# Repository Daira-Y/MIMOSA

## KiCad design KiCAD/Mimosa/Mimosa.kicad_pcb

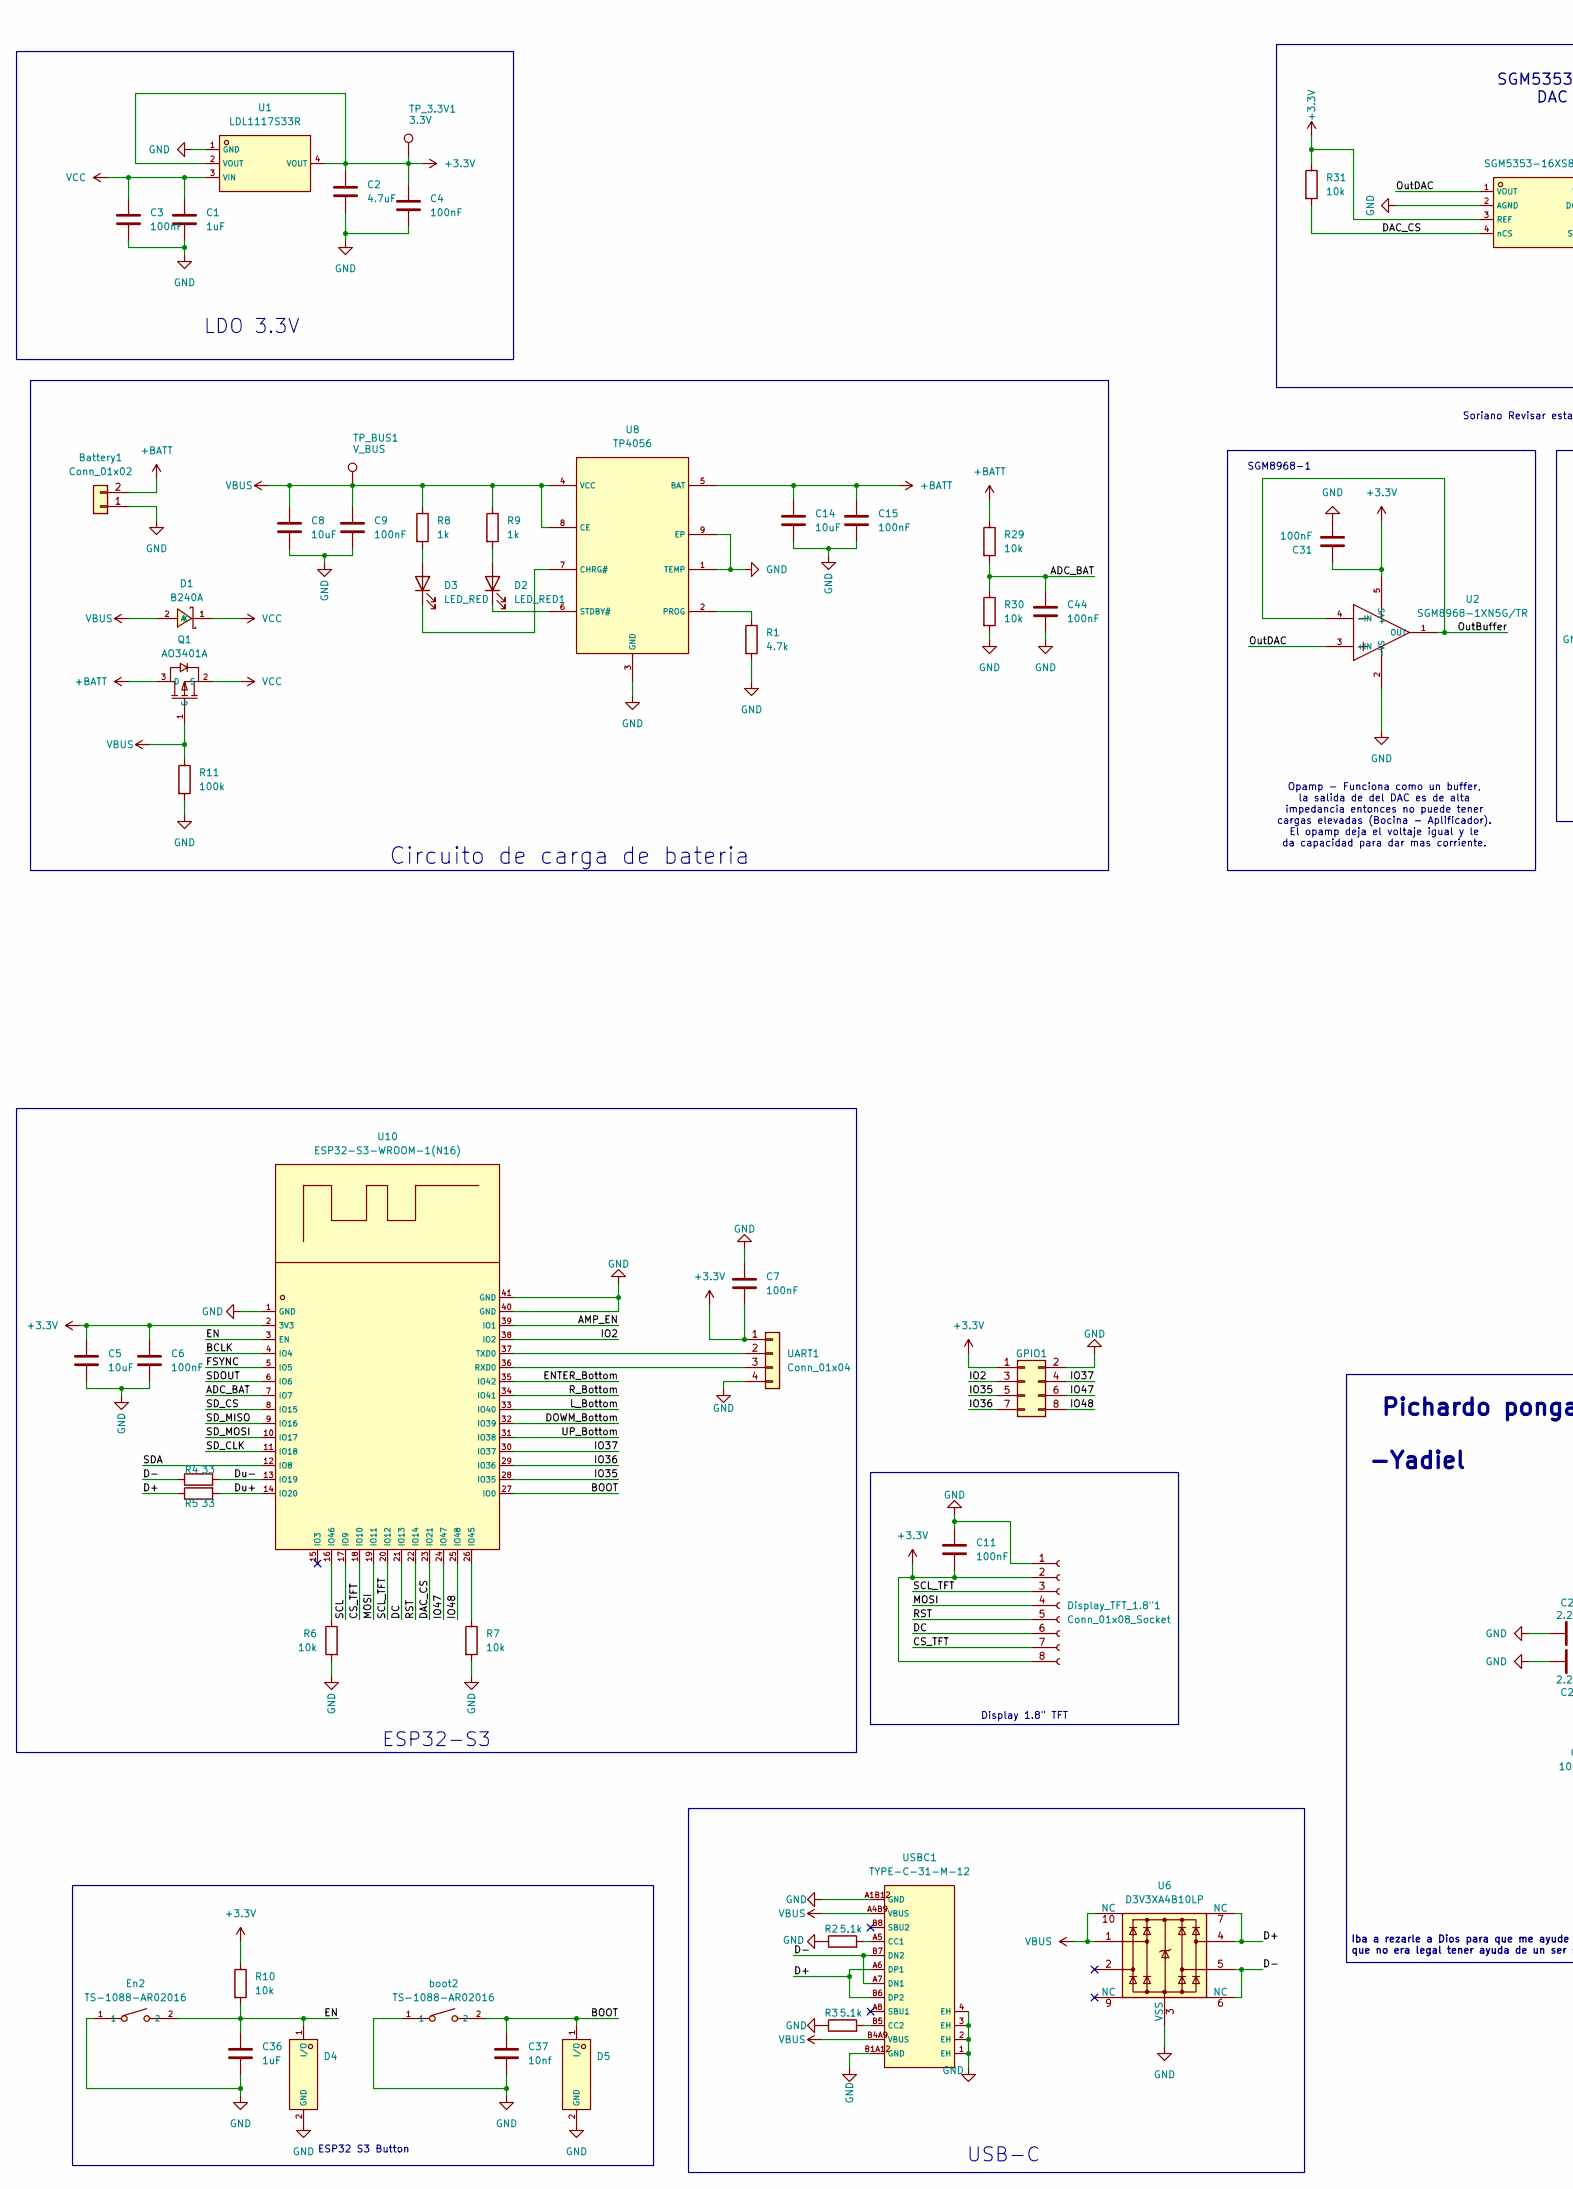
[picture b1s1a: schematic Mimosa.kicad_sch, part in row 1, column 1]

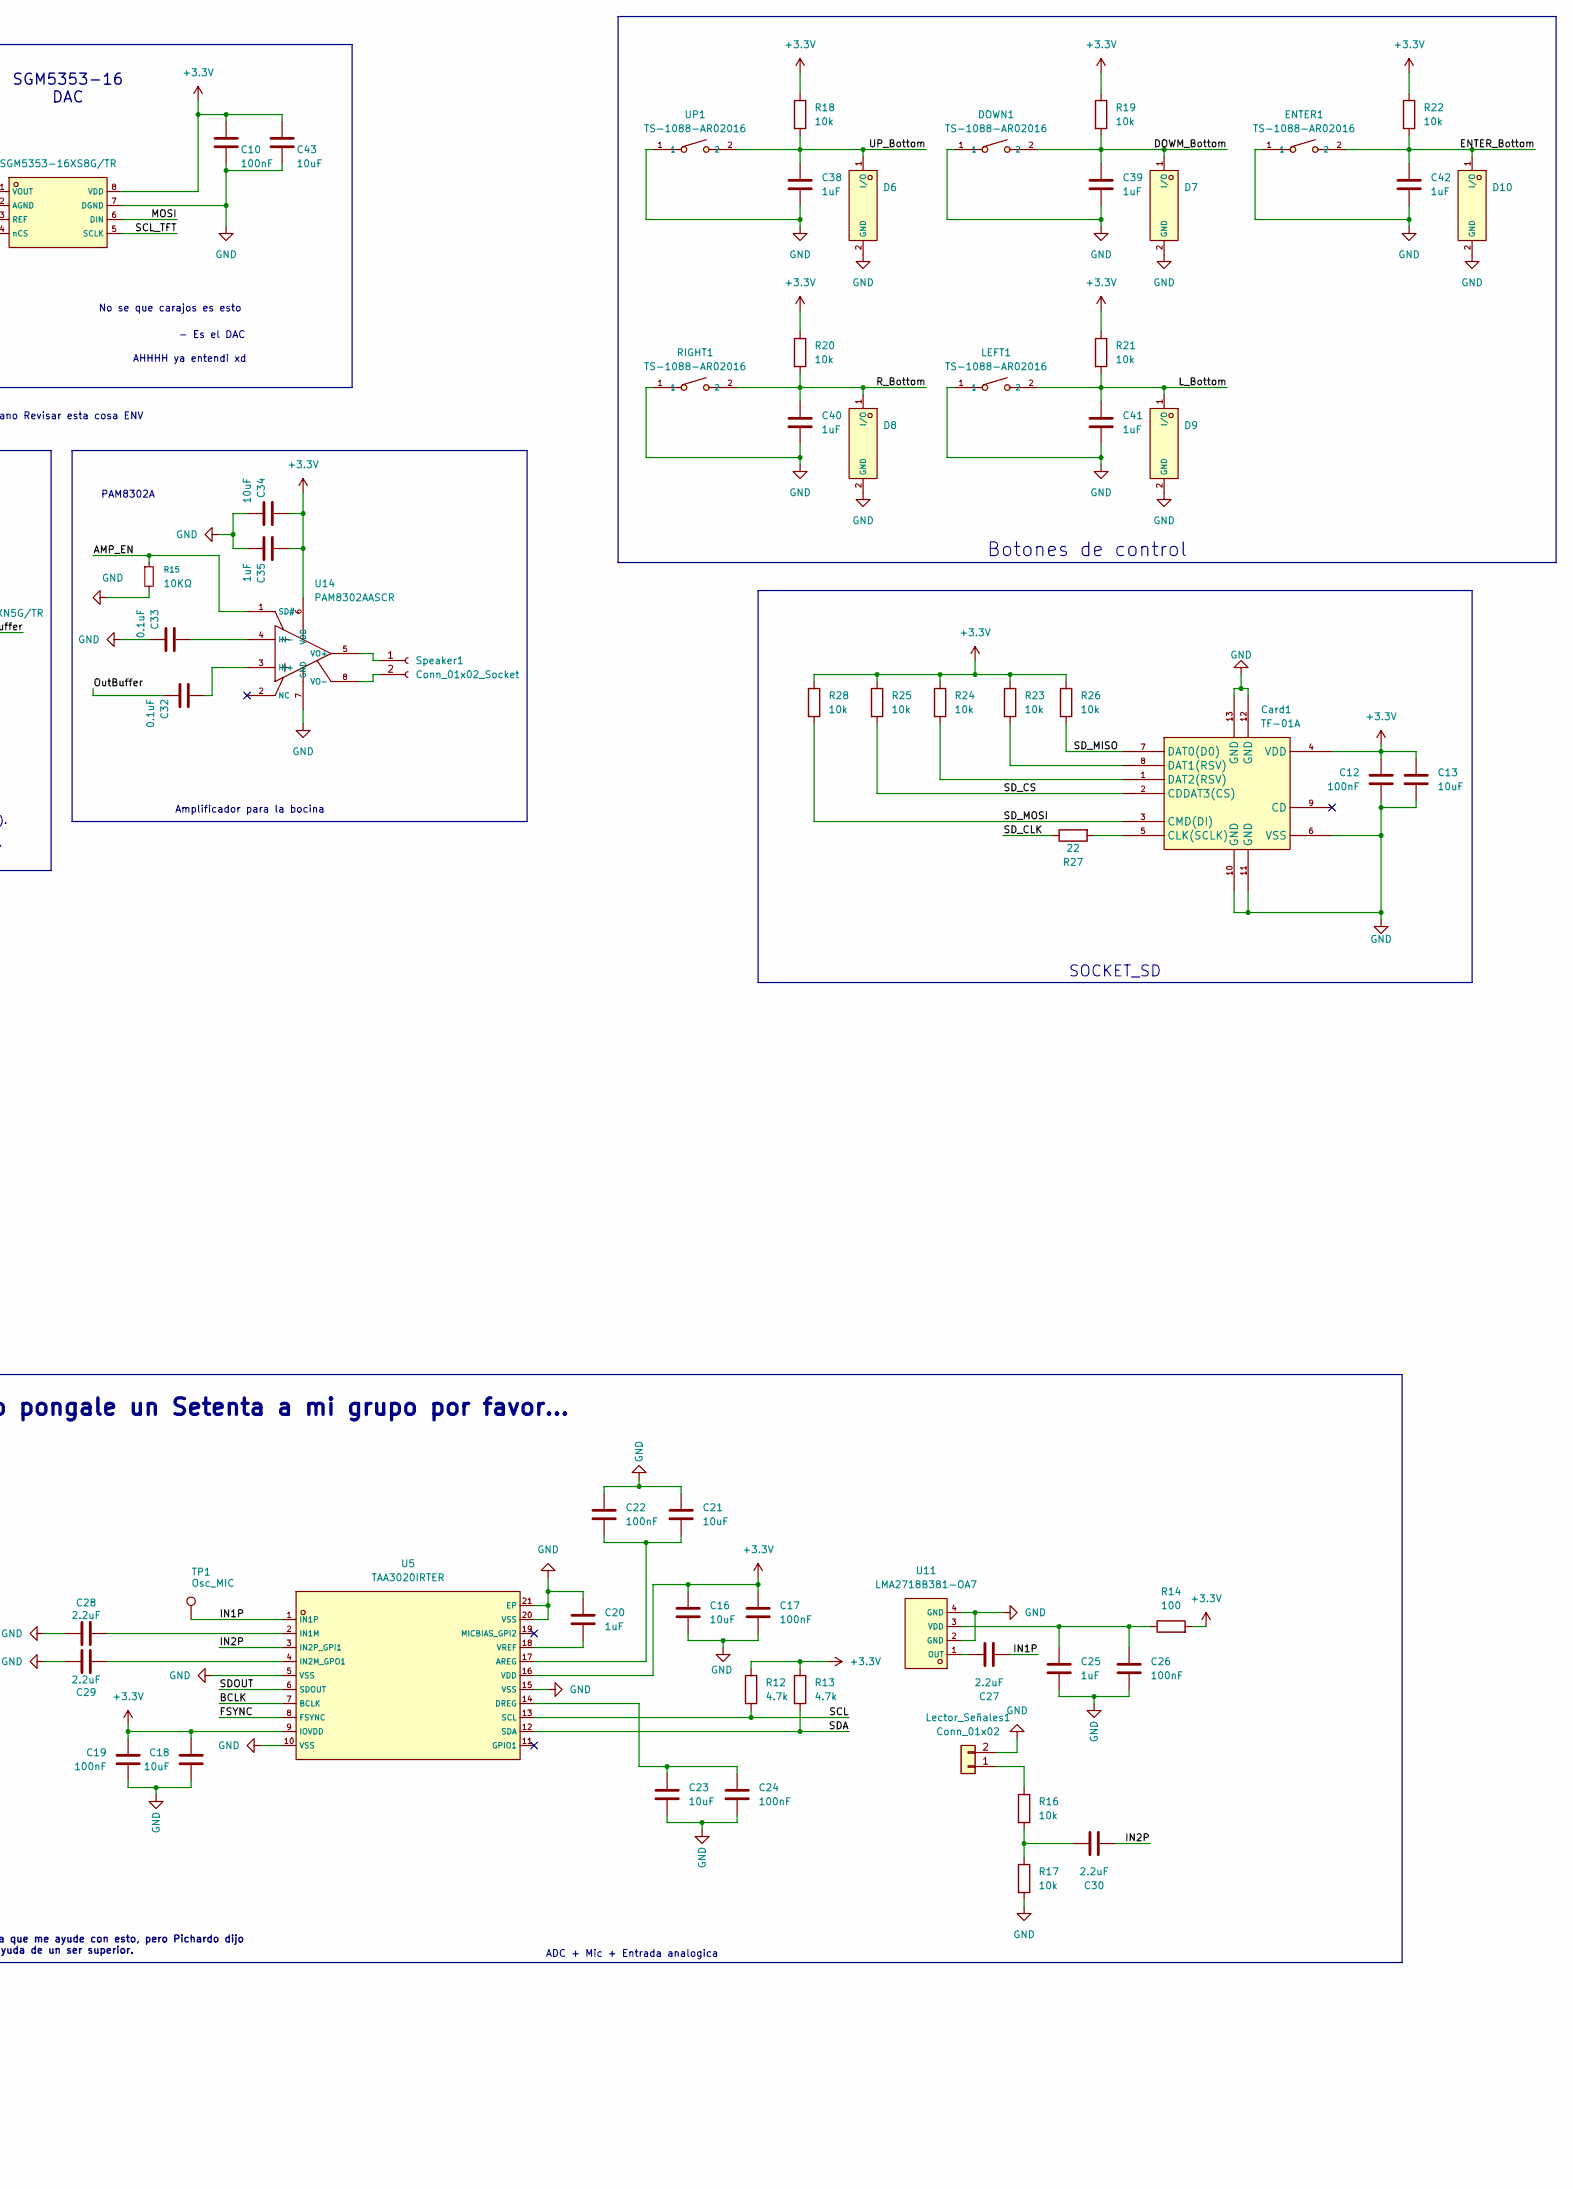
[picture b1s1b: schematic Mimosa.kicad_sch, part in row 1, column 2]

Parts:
Battery1: Conn_01x02; Molex_KK-254_AE-6410-02A_1x02_P2.54mm_Vertical
C1, C20, C25, C35, C36, C38, C39, C40, C41, C42: 1uF; C_0603_1608Metric
C2: 4.7uF; C_0603_1608Metric
C3, C4, C6, C7, C9, C10, C11, C12, C15, C17, C19, C22, C24, C26, C31, C44: 100nF; C_0603_1608Metric
C5, C8, C13, C14, C16, C18, C21, C23, C34, C43: 10uF; C_0603_1608Metric
C27, C28, C29, C30: 2.2uF; C_0603_1608Metric
C32, C33: 0.1uF; C_0603_1608Metric
C37: 10nf; C_0603_1608Metric
Card1: TF-01A; C91145_TF-SMD_TF-01A; LCSC C91145
D1: B240A; C39358_SMA_L4_3-W2_6-LS5_2-RD; LCSC C39358
D2: LED_RED1; LED_0805_2012Metric
D3: LED_RED; LED_0805_2012Metric
D4, D5, D6, D7, D8, D9, D10: ESD321DPYR_C2868952; C2868952_X1SON-2_L1_0-W0_6-P0_65-RD-1; LCSC C2868952
DOWN1: TS-1088-AR02016; C720477_SW-SMD_L3_9-W3_0-P4_45; LCSC C720477
Display_TFT_1.8"1: Conn_01x08_Socket; PinHeader_1x08_P2.54mm_Vertical
ENTER1: TS-1088-AR02016; C720477_SW-SMD_L3_9-W3_0-P4_45; LCSC C720477
En2: TS-1088-AR02016; C720477_SW-SMD_L3_9-W3_0-P4_45; LCSC C720477
GPIO1: Conn_02x04_Odd_Even; PinSocket_2x04_P2.54mm_Vertical
LEFT1: TS-1088-AR02016; C720477_SW-SMD_L3_9-W3_0-P4_45; LCSC C720477
Lector_Señales1: Conn_01x02; PinHeader_1x02_P2.54mm_Vertical
Q1: AO3401A; C15127_SOT-23_L2_9-W1_3-P1_90-LS2_4-BR; LCSC C15127
R1, R12, R13: 4.7k; R_0603_1608Metric
R2, R3: 5.1k; R_0603_1608Metric_Pad0.98x0.95mm_HandSolder
R4, R5: 33; R_0603_1608Metric
R6, R7, R10, R18, R19, R20, R21, R22: 10k; R_0603_1608Metric_Pad0.98x0.95mm_HandSolder
R8, R9: 1k; R_0603_1608Metric
R11: 100k; R_0603_1608Metric
R14: 100; R_0603_1608Metric
R15: 10KΩ; R_0603_1608Metric_Pad0.98x0.95mm_HandSolder
R16, R17, R23, R24, R25, R26, R28, R29, R30, R31: 10k; R_0603_1608Metric
R27: 22; R_0603_1608Metric
RIGHT1: TS-1088-AR02016; C720477_SW-SMD_L3_9-W3_0-P4_45; LCSC C720477
Speaker1: Conn_01x02_Socket; Molex_KK-254_AE-6410-02A_1x02_P2.54mm_Vertical
TP1: Osc_MIC; Pin_D0.7mm_L6.5mm_W1.8mm_FlatFork
TP_3.3V1: 3.3V; Pin_D0.7mm_L6.5mm_W1.8mm_FlatFork
TP_BUS1: V_BUS; Pin_D0.7mm_L6.5mm_W1.8mm_FlatFork
U1: LDL1117S33R; C435835_SOT-223-4_L6_5-W3_5-P2_30-LS7_0-BR; LCSC C435835
U2: SGM8968-1XN5G/TR; C700130_SOT-23-5_L2_9-W1_6-P0_95-LS2_8-BR; LCSC C700130
U3: SGM5353-16XS8G/TR; C5152099_SOIC-8_L4_9-W3_9-P1_27-LS6_0-BL; LCSC C5152099
U5: TAA3020IRTER; C43656725_WQFN-20_L3_0-W3_0-P0_50-TL-EP1_4; LCSC C43656725
U6: D3V3XA4B10LP; Diodes_UDFN-10_1x2.5mm_P0.5mm
U8: TP4056; C16581_ESOP-8_L4_9-W3_9-P1_27-LS6_0-BL-EP; LCSC C16581
U10: ESP32-S3-WROOM-1(N16); C2913199_WIRELM-SMD_ESP32-S3-WROOM-1; LCSC C2913199
U11: LMA2718B381-OA7; C5373222_MIC-SMD_4P-L2_8-W1_9_LMA2718B381-OA7; LCSC C5373222
U14: PAM8302AASCR; C113367_MSOP-8_L3_0-W3_0-P0_65-LS5_0-BL; LCSC C113367
UART1: Conn_01x04; PinHeader_1x04_P2.54mm_Vertical
UP1: TS-1088-AR02016; C720477_SW-SMD_L3_9-W3_0-P4_45; LCSC C720477
USBC1: TYPE-C-31-M-12; C165948_USB-C_SMD-TYPE-C-31-M-12_1; LCSC C165948
boot2: TS-1088-AR02016; C720477_SW-SMD_L3_9-W3_0-P4_45; LCSC C720477

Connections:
+3.3V: C2.1, C4.1, C5.1, C6.1, C7.2, C10.1, C11.2, C12.1, C13.1, C16.1, C17.1, C18.1, C19.1, C31.1, C34.1, C35.1, C43.1, Card1.4 (VDD), Display_TFT_1.8"1.2, Display_TFT_1.8"1.8, GPIO1.1, R10.1, R12.1, R13.1, R14.2, R18.1, R19.1, R20.1, R21.1, R22.1, R23.1, R24.1, R25.1, R26.1, R28.1, R31.1, TP_3.3V1.1 (1_1), U1.2 (VOUT), U1.4 (VOUT), U2.5 (+VS), U3.3 (REF), U3.8 (VDD), U5.9 (IOVDD), U5.16 (VDD), U10.2 (3V3), U14.6 (VDD), UART1.1
+BATT: Battery1.2, C14.1, C15.1, Q1.3 (D), R29.1, U8.5 (BAT)
/ADC_BAT: C44.1, R29.2, R30.1, U10.7 (IO7)
/AMP_EN: R15.1, U10.39 (IO1), U14.1 (SD#)
/BCLK: U5.7 (BCLK), U10.4 (IO4)
/BOOT: C37.1, D5.1 (I/O), U10.27 (IO0), boot2.2
/CS_TFT: Display_TFT_1.8"1.7, U10.18 (IO10)
/D+: R5.1, U6.4, U6.7 (NC), USBC1.A6 (DP1), USBC1.B6 (DP2)
/D-: R4.1, U6.5, U6.6 (NC), USBC1.A7 (DN1), USBC1.B7 (DN2)
/DAC_CS: R31.2, U3.4 (nCS), U10.23 (IO21)
/DC: Display_TFT_1.8"1.6, U10.21 (IO13)
/DOWM_Bottom: C39.1, D7.1 (I/O), DOWN1.2, R19.2, U10.32 (IO39)
/Du+: R5.2, U10.14 (IO20)
/Du-: R4.2, U10.13 (IO19)
/EN: C36.1, D4.1 (I/O), En2.2, R10.2, U10.3 (EN)
/ENTER_Bottom: C42.1, D10.1 (I/O), ENTER1.2, R22.2, U10.35 (IO42)
/FSYNC: U5.8 (FSYNC), U10.5 (IO5)
/IN1P: C27.2, TP1.1 (1_1), U5.1 (IN1P)
/IN2P: C30.2, U5.3 (IN2P_GPI1)
/IO2: GPIO1.3, U10.38 (IO2)
/IO35: GPIO1.5, U10.28 (IO35)
/IO36: GPIO1.7, U10.29 (IO36)
/IO37: GPIO1.4, U10.30 (IO37)
/IO47: GPIO1.6, U10.24 (IO47)
/IO48: GPIO1.8, U10.25 (IO48)
/L_Bottom: C41.1, D9.1 (I/O), LEFT1.2, R21.2, U10.33 (IO40)
/MOSI: Display_TFT_1.8"1.4, U3.6 (DIN), U10.19 (IO11)
/OutBuffer: C32.2, U2.1 (OUT), U2.4 (-IN)
/OutDAC: U2.3 (+IN), U3.1 (VOUT)
/RST: Display_TFT_1.8"1.5, U10.22 (IO14)
/R_Bottom: C40.1, D8.1 (I/O), R20.2, RIGHT1.2, U10.34 (IO41)
/SCL: R12.2, U5.13 (SCL), U10.17 (IO9)
/SCL_TFT: Display_TFT_1.8"1.3, U3.5 (SCLK), U10.20 (IO12)
/SDA: R13.2, U5.12 (SDA), U10.12 (IO8)
/SDOUT: U5.6 (SDOUT), U10.6 (IO6)
/SD_CLK: R27.1, U10.11 (IO18)
/SD_CS: Card1.2 (CDDAT3(CS)), R25.2, U10.8 (IO15)
/SD_MISO: Card1.7 (DAT0(D0)), R26.2, U10.9 (IO16)
/SD_MOSI: Card1.3 (CMD(DI)), R28.2, U10.10 (IO17)
/UP_Bottom: C38.1, D6.1 (I/O), R18.2, U10.31 (IO38), UP1.2
GND: Battery1.1, C1.2, C2.2, C3.2, C4.2, C5.2, C6.2, C7.1, C8.2, C9.2, C10.2, C11.1, C12.2, C13.2, C14.2, C15.2, C16.2, C17.2, C18.2, C19.2, C20.1, C21.2, C22.2, C23.2, C24.2, C25.2, C26.2, C28.1, C29.1, C31.2, C33.2, C34.2, C35.2, C36.2, C37.2, C38.2, C39.2, C40.2, C41.2, C42.2, C43.2, C44.2, Card1.6 (VSS), Card1.10 (GND), Card1.11 (GND), Card1.12 (GND), Card1.13 (GND), D4.2 (GND), D5.2 (GND), D6.2 (GND), D7.2 (GND), D8.2 (GND), D9.2 (GND), D10.2 (GND), DOWN1.1, Display_TFT_1.8"1.1, ENTER1.1, En2.1, GPIO1.2, LEFT1.1, Lector_Señales1.2, R1.2, R2.1, R3.1, R6.2, R7.2, R11.2, R15.2, R17.2, R30.2, RIGHT1.1, U1.1 (GND), U2.2 (-VS), U3.2 (AGND), U3.7 (DGND), U5.5 (VSS), U5.10 (VSS), U5.15 (VSS), U5.20 (VSS), U5.21 (EP), U6.3 (VSS), U6.8 (VSS), U8.1 (TEMP), U8.3 (GND), U8.9 (EP), U10.1 (GND), U10.40 (GND), U10.41 (GND), U11.2 (GND), U11.4 (GND), U14.7 (GND), UART1.4, UP1.1, USBC1.1 (EH), USBC1.2 (EH), USBC1.3 (EH), USBC1.4 (EH), USBC1.A1B12 (GND), USBC1.B1A12 (GND), boot2.1
unnamed: C30.1, R16.2, R17.1
unnamed: Card1.5 (CLK(SCLK)), R27.2
unnamed: Card1.8 (DAT1(RSV)), R23.2
unnamed: Card1.1 (DAT2(RSV)), R24.2
unnamed: D2.2 (A), R9.2
unnamed: D2.1 (K), U8.6 (STDBY#)
unnamed: D3.2 (A), R8.2
unnamed: D3.1 (K), U8.7 (CHRG#)
unnamed: Lector_Señales1.1, R16.1
unnamed: Speaker1.1, U14.5 (VO+)
unnamed: Speaker1.2, U14.8 (VO-)
unnamed: C21.1, C22.1, U5.17 (AREG)
unnamed: C23.1, C24.1, U5.14 (DREG)
unnamed: C28.2, U5.2 (IN1M)
unnamed: C29.2, U5.4 (IN2M_GPO1)
unnamed: C20.2, U5.18 (VREF)
unnamed: R1.1, U8.2 (PROG)
unnamed: R7.1, U10.26 (IO45)
unnamed: R6.1, U10.16 (IO46)
unnamed: U10.36 (RXD0), UART1.3
unnamed: U10.37 (TXD0), UART1.2
unnamed: C27.1, U11.1 (OUT)
unnamed: C25.1, C26.1, R14.1, U11.3 (VDD)
unnamed: C32.1, U14.3 (IN+)
unnamed: C33.1, U14.4 (IN-)
unnamed: R2.2, USBC1.A5 (CC1)
unnamed: R3.2, USBC1.B5 (CC2)
VBUS: C8.1, C9.1, D1.2 (A), Q1.1 (G), R8.1, R9.1, R11.1, TP_BUS1.1 (1_1), U6.1, U6.10 (NC), U8.4 (VCC), U8.8 (CE), USBC1.A4B9 (VBUS), USBC1.B4A9 (VBUS)
VCC: C1.1, C3.1, D1.1 (K), Q1.2 (S), U1.3 (VIN)

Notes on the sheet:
Pichardo pongale un Setenta a mi grupo por favor... -Yadiel
Amplificador para la bocina
Opamp - Funciona como un buffer, la salida de del DAC es de alta impedancia entonces no puede tener cargas elevadas (Bocina - Aplificador). El opamp deja el voltaje igual y le da capacidad para dar mas corriente.
USB-C
PAM8302A
SGM8968-1
Soriano Revisar esta cosa ENV
ESP32 S3 Button
Iba a rezarle a Dios para que me ayude con esto, pero Pichardo dijo que no era legal tener ayuda de un ser superior.
AHHHH ya entendi xd
No se que carajos es esto
LDO 3.3V
SGM5353-16 DAC
- Es el DAC
ADC + Mic + Entrada analogica
Botones de control
ESP32-S3
SOCKET_SD
Display 1.8" TFT
Circuito de carga de bateria

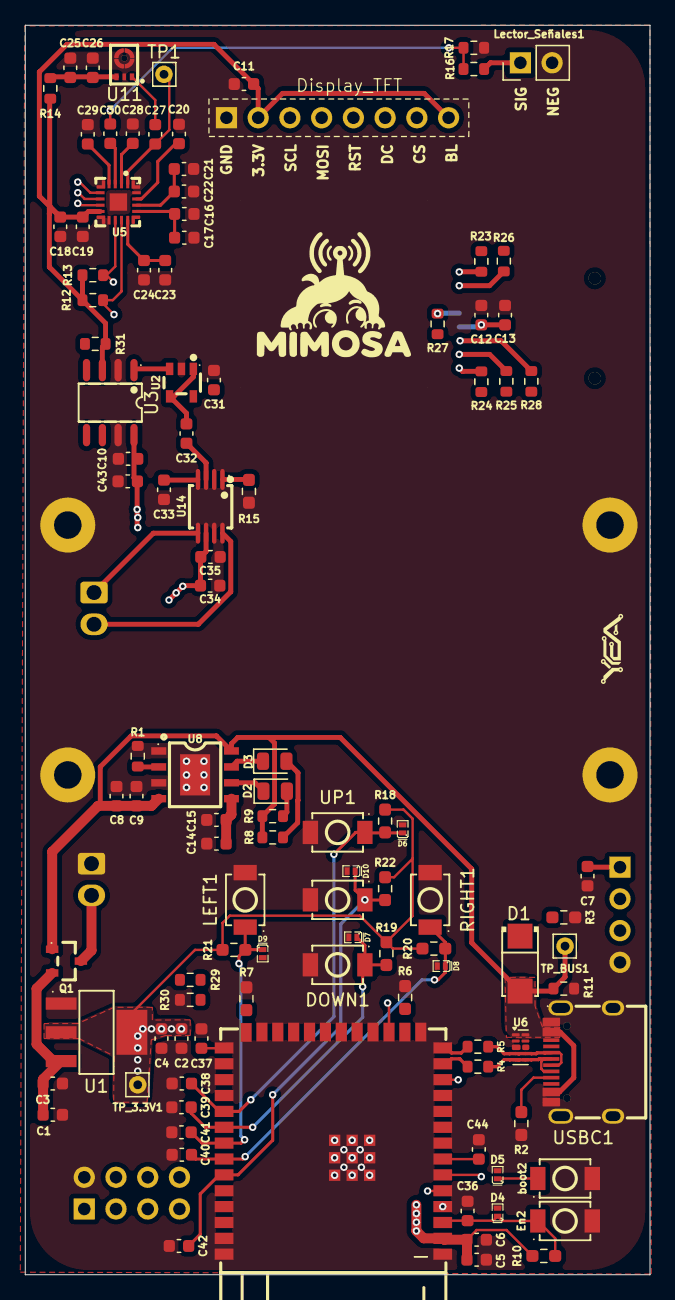
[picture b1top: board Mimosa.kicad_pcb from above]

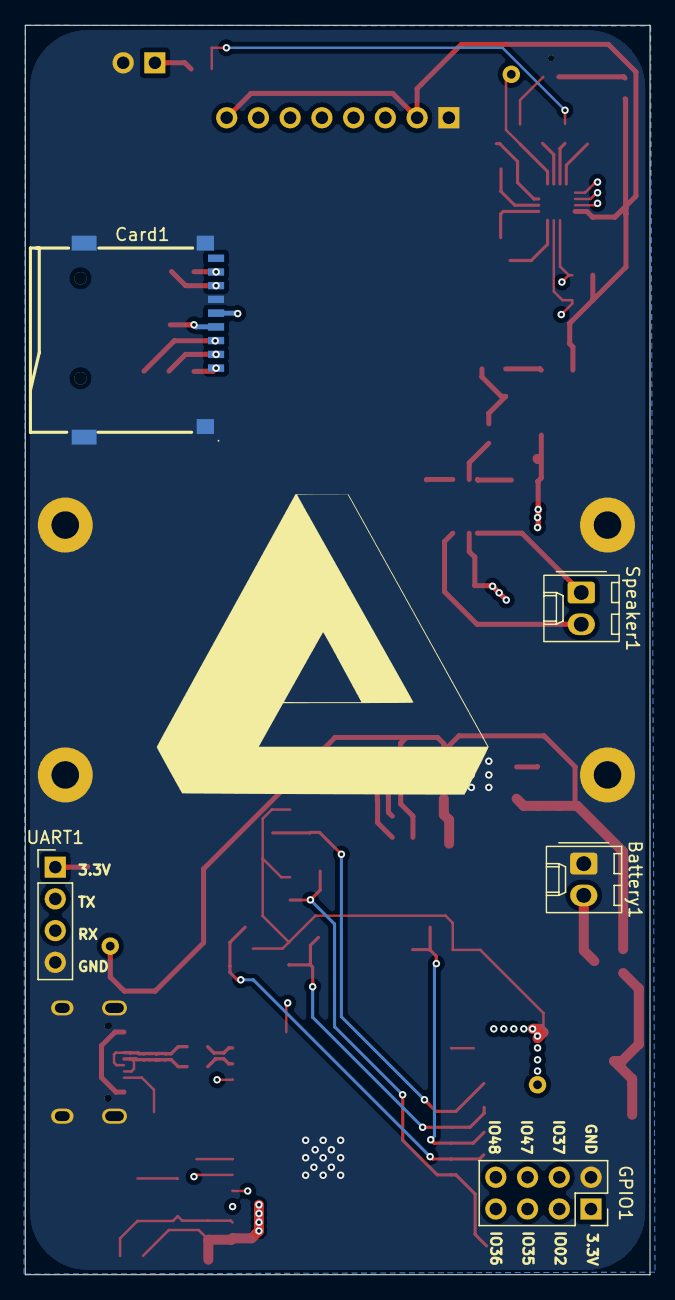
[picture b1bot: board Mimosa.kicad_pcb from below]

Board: 4 copper layers, 50.0 x 100.0 mm, 113 parts (5 on the bottom side), 70 nets.
